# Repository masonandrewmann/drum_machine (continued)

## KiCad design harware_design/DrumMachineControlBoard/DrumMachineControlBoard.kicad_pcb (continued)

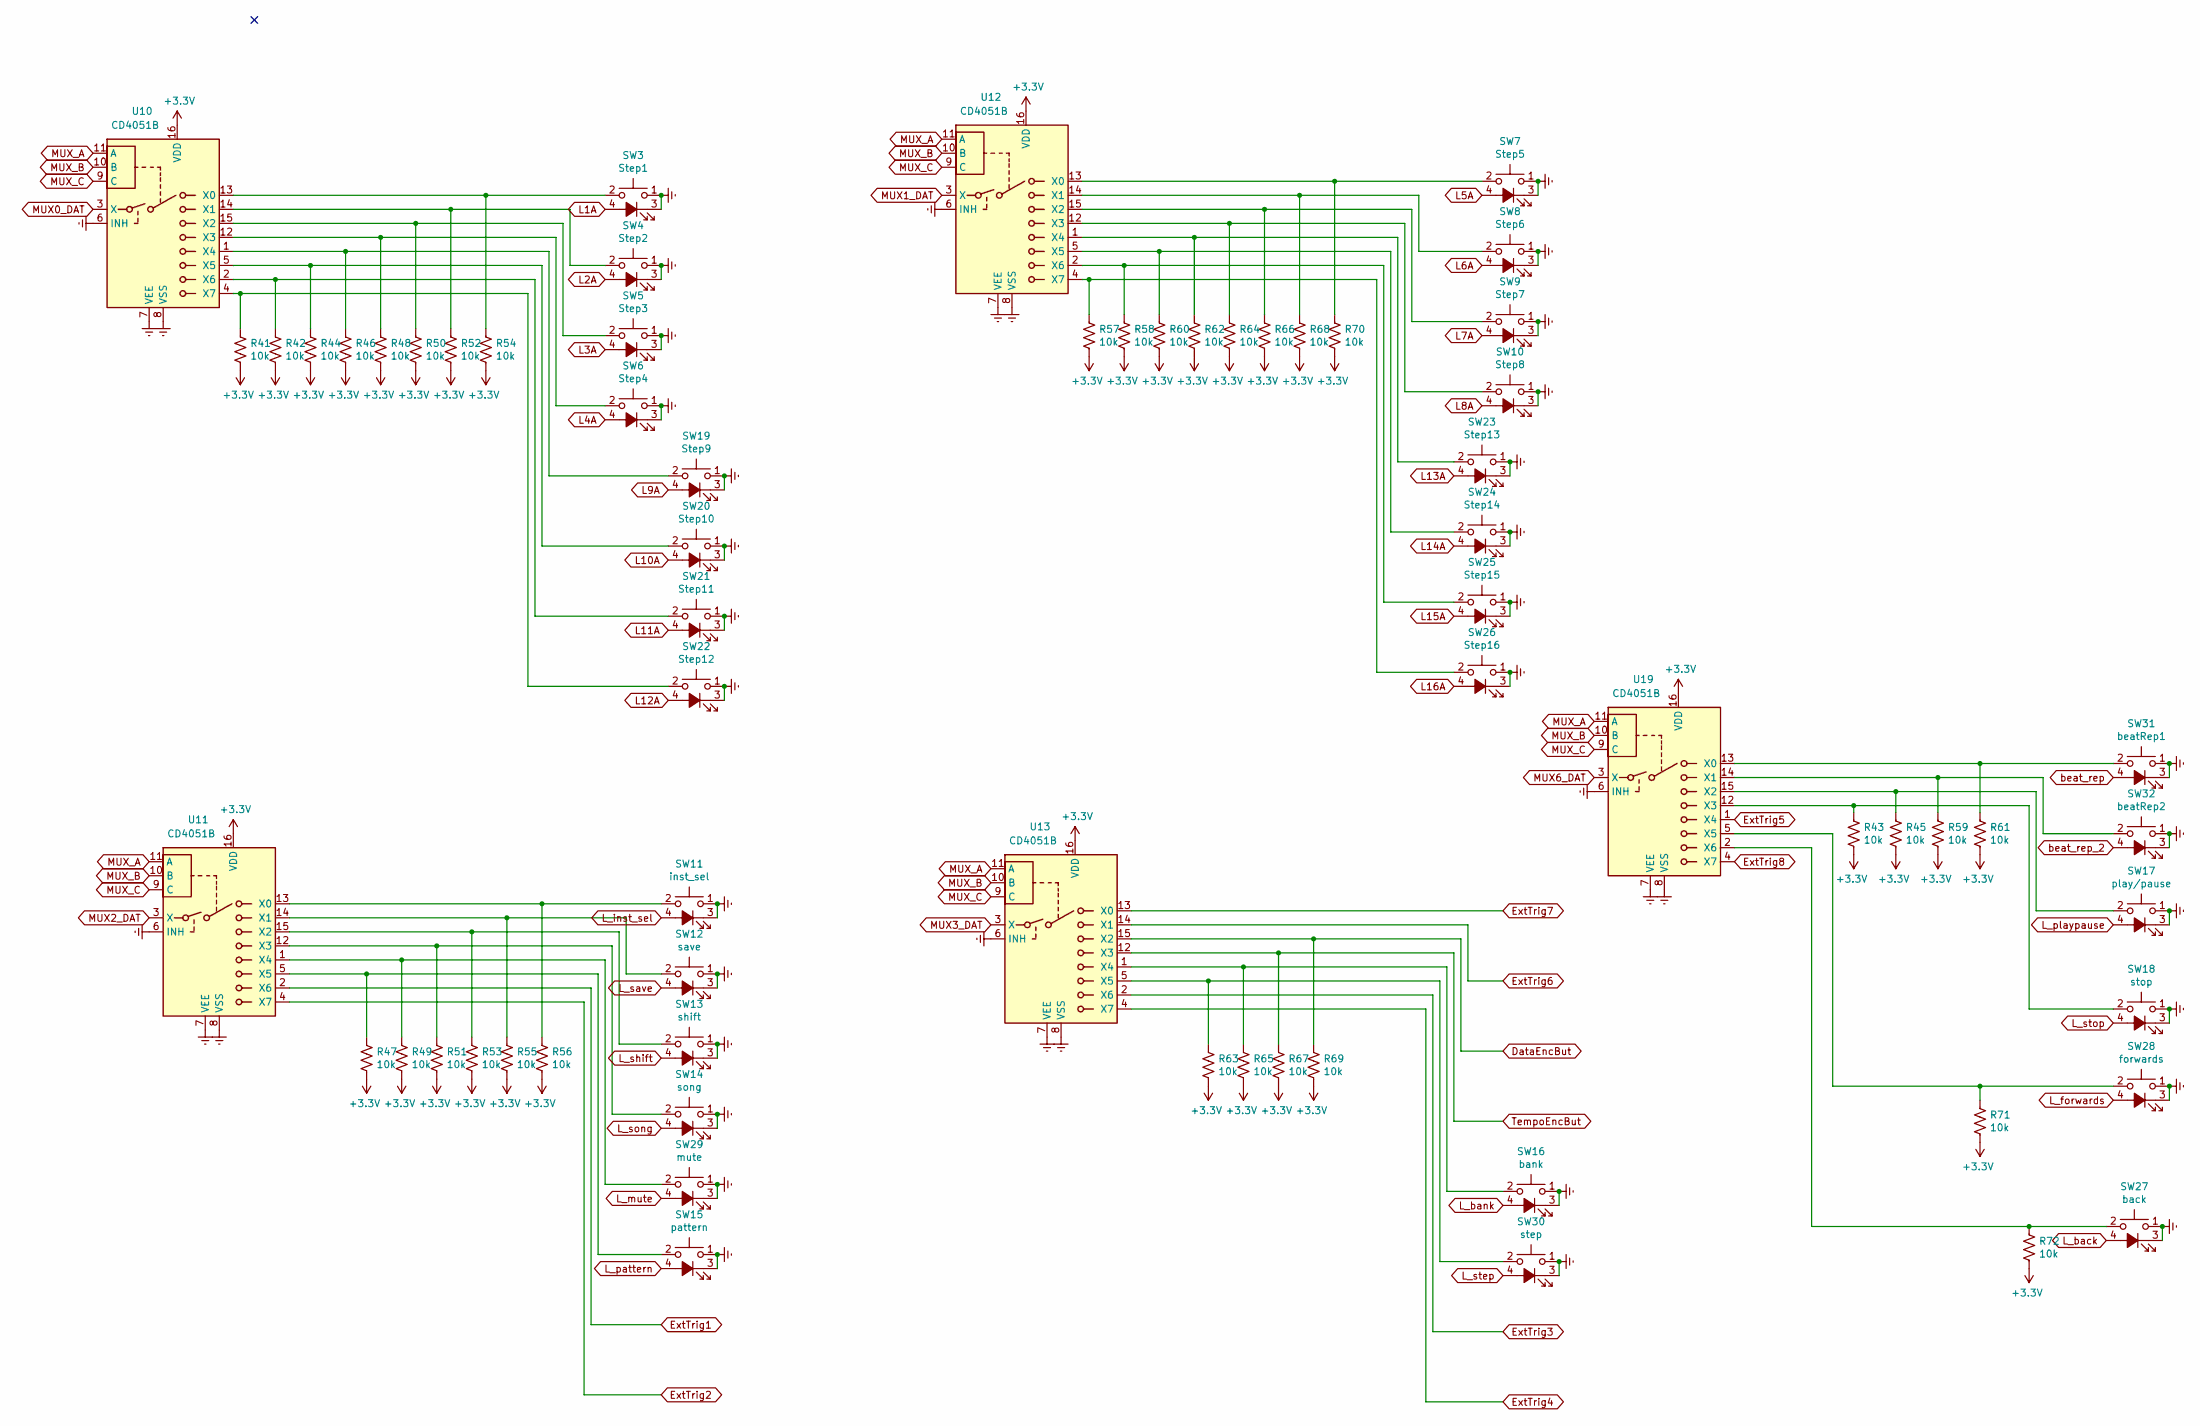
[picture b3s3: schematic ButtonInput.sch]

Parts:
R41, R42, R43, R44, R45, R46, R47, R48, R49, R50, R51, R52, R53, R54, R55, R56, R57, R58, R59, R60, R61, R62, R63, R64, R65, R66, R67, R68, R69, R70, R71, R72: 10k; R_0805_2012Metric_Pad1.15x1.40mm_HandSolder
SW3: Step1; CFPB-1CC-5G9
SW4: Step2; CFPB-1CC-5G9
SW5: Step3; CFPB-1CC-5G9
SW6: Step4; CFPB-1CC-5G9
SW7: Step5; CFPB-1CC-5G9
SW8: Step6; CFPB-1CC-5G9
SW9: Step7; CFPB-1CC-5G9
SW10: Step8; CFPB-1CC-5G9
SW11: inst_sel; CFPB-1CC-5G9
SW12: save; CFPB-1CC-5G9
SW13: shift; CFPB-1CC-5G9
SW14: song; CFPB-1CC-5G9
SW15: pattern; CFPB-1CC-5G9
SW16: bank; CFPB-1CC-5G9
SW17: play/pause; CFPB-1CC-5G9
SW18: stop; CFPB-1CC-5G9
SW19: Step9; CFPB-1CC-5G9
SW20: Step10; CFPB-1CC-5G9
SW21: Step11; CFPB-1CC-5G9
SW22: Step12; CFPB-1CC-5G9
SW23: Step13; CFPB-1CC-5G9
SW24: Step14; CFPB-1CC-5G9
SW25: Step15; CFPB-1CC-5G9
SW26: Step16; CFPB-1CC-5G9
SW27: back; CFPB-1CC-5G9
SW28: forwards; CFPB-1CC-5G9
SW29: mute; CFPB-1CC-5G9
SW30: step; CFPB-1CC-5G9
SW31: beatRep1; CFPB-1CC-5G9
SW32: beatRep2; CFPB-1CC-5G9
U10, U11, U12, U13, U19: CD4051B; SOIC-16_3.9x9.9mm_P1.27mm

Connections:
+3V3: R41.1, R42.1, R43.1, R44.1, R45.1, R46.1, R47.1, R48.1, R49.1, R50.1, R51.1, R52.1, R53.1, R54.1, R55.1, R56.1, R57.1, R58.1, R59.1, R60.1, R61.1, R62.1, R63.1, R64.1, R65.1, R66.1, R67.1, R68.1, R69.1, R70.1, R71.1, R72.1, U10.16 (VDD), U11.16 (VDD), U12.16 (VDD), U13.16 (VDD), U19.16 (VDD); also elsewhere on the board
DataEncBut: R69.2, U13.15 (X2); also elsewhere on the board
ExtTrig1: U11.2 (X6); also elsewhere on the board
ExtTrig2: U11.4 (X7); also elsewhere on the board
ExtTrig3: U13.2 (X6); also elsewhere on the board
ExtTrig4: U13.4 (X7); also elsewhere on the board
ExtTrig5: U19.1 (X4); also elsewhere on the board
ExtTrig6: U13.14 (X1); also elsewhere on the board
ExtTrig7: U13.13 (X0); also elsewhere on the board
ExtTrig8: U19.4 (X7); also elsewhere on the board
L1A: SW3.4 (A); also elsewhere on the board
L2A: SW4.4 (A); also elsewhere on the board
L3A: SW5.4 (A); also elsewhere on the board
L4A: SW6.4 (A); also elsewhere on the board
L5A: SW7.4 (A); also elsewhere on the board
L6A: SW8.4 (A); also elsewhere on the board
L7A: SW9.4 (A); also elsewhere on the board
L8A: SW10.4 (A); also elsewhere on the board
L9A: SW19.4 (A); also elsewhere on the board
L10A: SW20.4 (A); also elsewhere on the board
L11A: SW21.4 (A); also elsewhere on the board
L12A: SW22.4 (A); also elsewhere on the board
L13A: SW23.4 (A); also elsewhere on the board
L14A: SW24.4 (A); also elsewhere on the board
L15A: SW25.4 (A); also elsewhere on the board
L16A: SW26.4 (A); also elsewhere on the board
L_back: SW27.4 (A); also elsewhere on the board
L_bank: SW16.4 (A); also elsewhere on the board
L_forwards: SW28.4 (A); also elsewhere on the board
L_inst_sel: SW11.4 (A); also elsewhere on the board
L_mute: SW29.4 (A); also elsewhere on the board
L_pattern: SW15.4 (A); also elsewhere on the board
L_playpause: SW17.4 (A); also elsewhere on the board
L_save: SW12.4 (A); also elsewhere on the board
L_shift: SW13.4 (A); also elsewhere on the board
L_song: SW14.4 (A); also elsewhere on the board
L_step: SW30.4 (A); also elsewhere on the board
L_stop: SW18.4 (A); also elsewhere on the board
MUX0_DAT: U10.3 (X); also elsewhere on the board
MUX1_DAT: U12.3 (X); also elsewhere on the board
MUX2_DAT: U11.3 (X); also elsewhere on the board
MUX3_DAT: U13.3 (X); also elsewhere on the board
MUX6_DAT: U19.3 (X); also elsewhere on the board
MUX_A: U10.11 (A), U11.11 (A), U12.11 (A), U13.11 (A), U19.11 (A); also elsewhere on the board
MUX_B: U10.10 (B), U11.10 (B), U12.10 (B), U13.10 (B), U19.10 (B); also elsewhere on the board
MUX_C: U10.9 (C), U11.9 (C), U12.9 (C), U13.9 (C), U19.9 (C); also elsewhere on the board
unnamed: R41.2, SW22.2, U10.4 (X7)
unnamed: R42.2, SW21.2, U10.2 (X6)
unnamed: R43.2, SW18.2, U19.12 (X3)
unnamed: R44.2, SW20.2, U10.5 (X5)
unnamed: R45.2, SW17.2, U19.15 (X2)
unnamed: R46.2, SW19.2, U10.1 (X4)
unnamed: R47.2, SW15.2, U11.5 (X5)
unnamed: R48.2, SW6.2, U10.12 (X3)
unnamed: R49.2, SW29.2, U11.1 (X4)
unnamed: R50.2, SW5.2, U10.15 (X2)
unnamed: R51.2, SW14.2, U11.12 (X3)
unnamed: R52.2, SW4.2, U10.14 (X1)
unnamed: R53.2, SW13.2, U11.15 (X2)
unnamed: R54.2, SW3.2, U10.13 (X0)
unnamed: R55.2, SW12.2, U11.14 (X1)
unnamed: R56.2, SW11.2, U11.13 (X0)
unnamed: R57.2, SW26.2, U12.4 (X7)
unnamed: R58.2, SW25.2, U12.2 (X6)
unnamed: R59.2, SW32.2, U19.14 (X1)
unnamed: R60.2, SW24.2, U12.5 (X5)
unnamed: R61.2, SW31.2, U19.13 (X0)
unnamed: R62.2, SW23.2, U12.1 (X4)
unnamed: R63.2, SW30.2, U13.5 (X5)
unnamed: R64.2, SW10.2, U12.12 (X3)
unnamed: R65.2, SW16.2, U13.1 (X4)
unnamed: R66.2, SW9.2, U12.15 (X2)
unnamed: R68.2, SW8.2, U12.14 (X1)
unnamed: R70.2, SW7.2, U12.13 (X0)
unnamed: R71.2, SW28.2, U19.5 (X5)
unnamed: R72.2, SW27.2, U19.2 (X6)
TempoEncBut: R67.2, U13.12 (X3); also elsewhere on the board
beat_rep: SW31.4 (A); also elsewhere on the board
beat_rep_2: SW32.4 (A); also elsewhere on the board

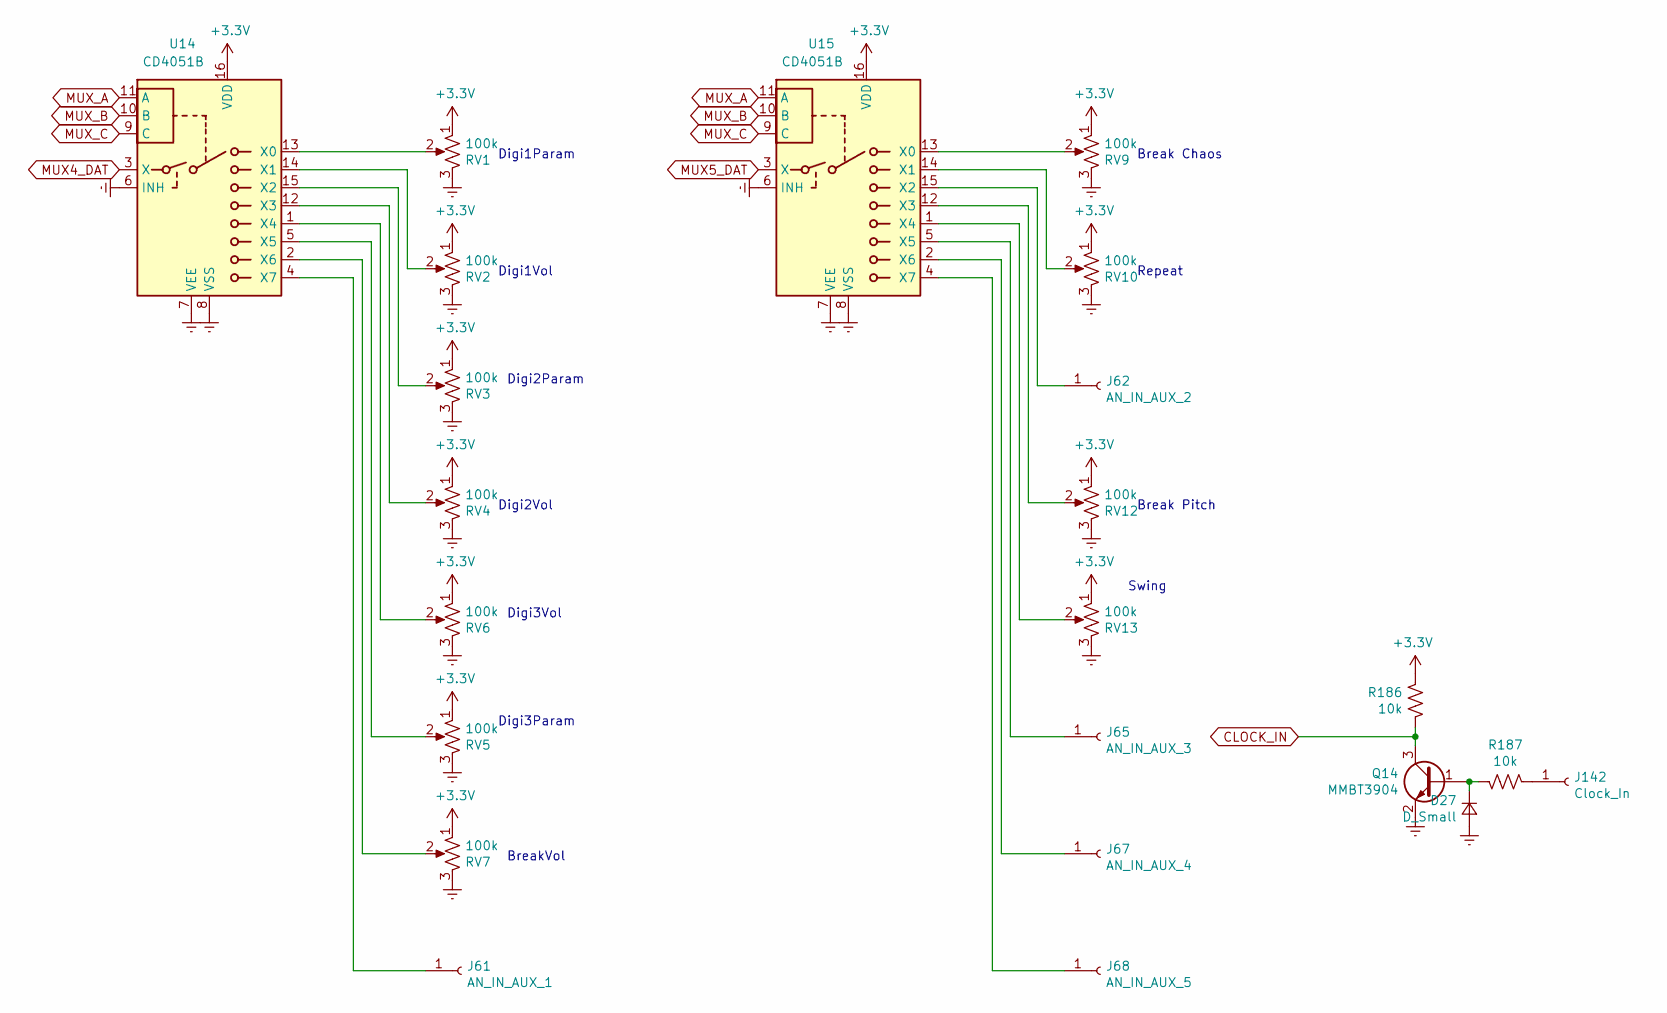
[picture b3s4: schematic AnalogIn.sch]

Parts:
D27: D_Small; D_SOD-123
J61: AN_IN_AUX_1; SolderWirePad_1x01_Drill1mm
J62: AN_IN_AUX_2; SolderWirePad_1x01_Drill1mm
J65: AN_IN_AUX_3; SolderWirePad_1x01_Drill1mm
J67: AN_IN_AUX_4; SolderWirePad_1x01_Drill1mm
J68: AN_IN_AUX_5; SolderWirePad_1x01_Drill1mm
J142: Clock_In; SolderWirePad_1x01_Drill1mm
Q14: MMBT3904; SOT-23
R186, R187: 10k; R_0603_1608Metric_Pad1.05x0.95mm_HandSolder
RV1, RV2, RV3, RV4, RV5, RV6, RV7, RV9, RV10, RV12, RV13: 100k; masonsPotentiometer_Alpha_RD901F-40-00D_Single_Vertical
U14, U15: CD4051B; SOIC-16_3.9x9.9mm_P1.27mm

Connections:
+3V3: R186.2, RV1.1, RV2.1, RV3.1, RV4.1, RV5.1, RV6.1, RV7.1, RV9.1, RV10.1, RV12.1, RV13.1, U14.16 (VDD), U15.16 (VDD); also elsewhere on the board
CLOCK_IN: Q14.3 (C), R186.1; also elsewhere on the board
MUX4_DAT: U14.3 (X); also elsewhere on the board
MUX5_DAT: U15.3 (X); also elsewhere on the board
MUX_A: U14.11 (A), U15.11 (A); also elsewhere on the board
MUX_B: U14.10 (B), U15.10 (B); also elsewhere on the board
MUX_C: U14.9 (C), U15.9 (C); also elsewhere on the board
unnamed: D27.1 (K), Q14.1 (B), R187.1
unnamed: J61.1, U14.4 (X7)
unnamed: J62.1, U15.15 (X2)
unnamed: J65.1, U15.5 (X5)
unnamed: J67.1, U15.2 (X6)
unnamed: J68.1, U15.4 (X7)
unnamed: J142.1, R187.2
unnamed: RV1.2, U14.13 (X0)
unnamed: RV2.2, U14.14 (X1)
unnamed: RV3.2, U14.15 (X2)
unnamed: RV4.2, U14.12 (X3)
unnamed: RV5.2, U14.5 (X5)
unnamed: RV6.2, U14.1 (X4)
unnamed: RV7.2, U14.2 (X6)
unnamed: RV9.2, U15.13 (X0)
unnamed: RV10.2, U15.14 (X1)
unnamed: RV12.2, U15.12 (X3)
unnamed: RV13.2, U15.1 (X4)

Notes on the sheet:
Digi1Param
Digi2Param
Digi3Param
Digi1Vol
Digi2Vol
Digi3Vol
BreakVol
Break Chaos
Repeat
Break Pitch
Swing

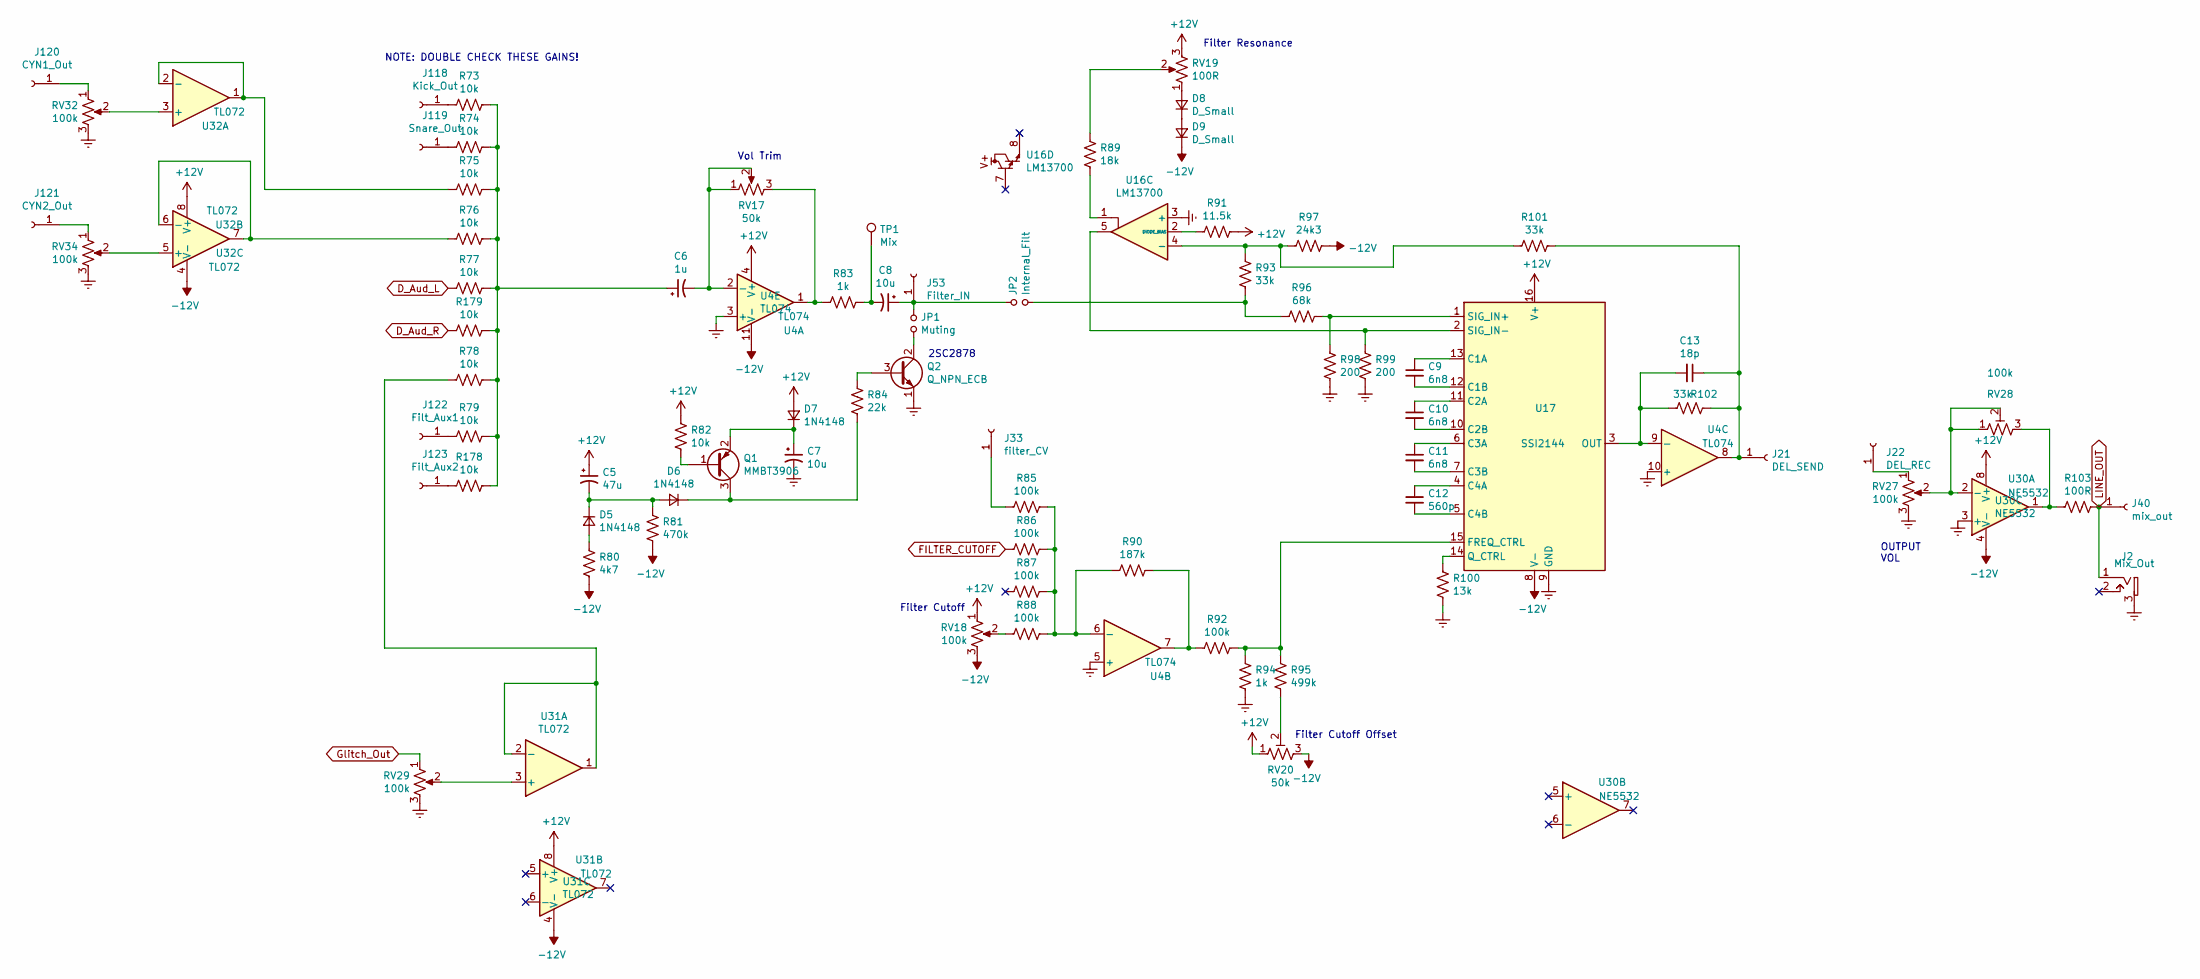
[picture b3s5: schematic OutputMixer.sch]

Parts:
C5: 47u; CP_Elec_6.3x7.7
C6: 1u; CP_Elec_4x4.5
C7, C8: 10u; CP_Elec_4x4.5
C9, C10, C11: 6n8; C_0805_2012Metric_Pad1.15x1.40mm_HandSolder
C12: 560p; C_0805_2012Metric_Pad1.15x1.40mm_HandSolder
C13: 18p; C_0805_2012Metric_Pad1.15x1.40mm_HandSolder
D5, D6, D7: 1N4148; D_SOD-123
D8, D9: D_Small; D_SOD-123
J2: Mix_Out; SolderWirePad_1x01_Drill1mm
J21: DEL_SEND; SolderWirePad_1x01_Drill1mm
J22: DEL_REC; SolderWirePad_1x01_Drill1mm
J33: filter_CV; SolderWirePad_1x01_Drill1mm
J40: mix_out; SolderWirePad_1x01_Drill1mm
J53: Filter_IN; SolderWirePad_1x01_Drill1mm
J118: Kick_Out; SolderWirePad_1x01_Drill1mm
J119: Snare_Out; SolderWirePad_1x01_Drill1mm
J120: CYN1_Out; SolderWirePad_1x01_Drill1mm
J121: CYN2_Out; SolderWirePad_1x01_Drill1mm
J122: Filt_Aux1; SolderWirePad_1x01_Drill1mm
J123: Filt_Aux2; SolderWirePad_1x01_Drill1mm
JP1: Muting; SolderJumper-2_P1.3mm_Open_RoundedPad1.0x1.5mm
JP2: Internal_Filt; SolderJumper-2_P1.3mm_Open_RoundedPad1.0x1.5mm
Q1: MMBT3906; SOT-23
Q2: Q_NPN_ECB; TO-92_Inline_Wide
R73, R74, R75, R76, R77, R78, R79, R82, R178, R179: 10k; R_0805_2012Metric_Pad1.15x1.40mm_HandSolder
R80: 4k7; R_0805_2012Metric_Pad1.15x1.40mm_HandSolder
R81: 470k; R_0805_2012Metric_Pad1.15x1.40mm_HandSolder
R83, R94: 1k; R_0805_2012Metric_Pad1.15x1.40mm_HandSolder
R84: 22k; R_0805_2012Metric_Pad1.15x1.40mm_HandSolder
R85, R86, R87, R88, R92: 100k; R_0805_2012Metric_Pad1.15x1.40mm_HandSolder
R89: 18k; R_0805_2012Metric_Pad1.15x1.40mm_HandSolder
R90: 187k; R_0805_2012Metric_Pad1.15x1.40mm_HandSolder
R91: 11.5k; R_0805_2012Metric_Pad1.15x1.40mm_HandSolder
R93, R101, R102: 33k; R_0805_2012Metric_Pad1.15x1.40mm_HandSolder
R95: 499k; R_0805_2012Metric_Pad1.15x1.40mm_HandSolder
R96: 68k; R_0805_2012Metric_Pad1.15x1.40mm_HandSolder
R97: 24k3; R_0805_2012Metric_Pad1.15x1.40mm_HandSolder
R98, R99: 200; R_0805_2012Metric_Pad1.15x1.40mm_HandSolder
R100: 13k; R_0805_2012Metric_Pad1.15x1.40mm_HandSolder
R103: 100R; R_0805_2012Metric_Pad1.15x1.40mm_HandSolder
RV17, RV20: 50k; Potentiometer_Runtron_RM-065_Vertical
RV18, RV27, RV29, RV32, RV34: 100k; masonsPotentiometer_Alpha_RD901F-40-00D_Single_Vertical
RV19: 100R; masonsPotentiometer_Alpha_RD901F-40-00D_Single_Vertical
RV28: 100k; Potentiometer_Runtron_RM-065_Vertical
TP1: Mix; TestPoint_Loop_D2.50mm_Drill1.0mm
U4: TL074; SOIC-14_3.9x8.7mm_P1.27mm
U16: LM13700; SOIC-16_3.9x9.9mm_P1.27mm
U17: SSI2144; SSOP-16_3.9x4.9mm_P0.635mm
U30: NE5532; DIP-8_W7.62mm_Socket
U31, U32: TL072; SOIC-8_3.9x4.9mm_P1.27mm

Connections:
-12V: D9.1 (K), R80.1, R81.1, R97.1, RV18.3, RV20.3, U4.11 (V-), U17.8 (V-), U30.4 (V-), U31.4 (V-), U32.4 (V-); also elsewhere on the board
D_Aud_L: R77.2; also elsewhere on the board
D_Aud_R: R179.2; also elsewhere on the board
FILTER_CUTOFF: R86.2; also elsewhere on the board
Glitch_Out: RV29.1; also elsewhere on the board
unnamed: C5.2, D5.1 (K), D6.2 (A), R81.2
unnamed: C6.1, R73.1, R74.1, R75.1, R76.1, R77.1, R78.1, R79.1, R178.1, R179.1
unnamed: C6.2, RV17.1, RV17.2, U4.2 (-)
unnamed: C7.1, D7.1 (K), Q1.2 (E)
unnamed: C8.1, J53.1, JP1.1, JP2.1
unnamed: C8.2, R83.1, TP1.1
unnamed: C9.1, U17.13 (C1A)
unnamed: C9.2, U17.12 (C1B)
unnamed: C10.1, U17.11 (C2A)
unnamed: C10.2, U17.10 (C2B)
unnamed: C11.1, U17.6 (C3A)
unnamed: C11.2, U17.7 (C3B)
unnamed: C12.1, U17.4 (C4A)
unnamed: C12.2, U17.5 (C4B)
unnamed: C13.1, J21.1, R101.1, R102.2, U4.8
unnamed: C13.2, R102.1, U4.9 (-), U17.3 (OUT)
unnamed: D5.2 (A), R80.2
unnamed: D6.1 (K), Q1.3 (C), R84.1
unnamed: D8.1 (K), D9.2 (A)
unnamed: D8.2 (A), RV19.1
unnamed: J22.1, RV27.1
unnamed: J33.1, R85.2
unnamed: J118.1, R73.2
unnamed: J119.1, R74.2
unnamed: J120.1, RV32.1
unnamed: J121.1, RV34.1
unnamed: J122.1, R79.2
unnamed: J123.1, R178.2
unnamed: JP1.2, Q2.2 (C)
unnamed: JP2.2, R93.2, R96.1
unnamed: Q1.1 (B), R82.1
unnamed: Q2.3 (B), R84.2
unnamed: R75.2, U32.1, U32.2 (-)
unnamed: R76.2, U32.6 (-), U32.7
unnamed: R78.2, U31.1, U31.2 (-)
unnamed: R83.2, RV17.3, U4.1
unnamed: R85.1, R86.1, R87.1, R88.1, R90.2, U4.6 (-)
unnamed: R88.2, RV18.2
unnamed: R89.1, RV19.2
unnamed: R89.2, U16.1
unnamed: R90.1, R92.2, U4.7
unnamed: R91.2, U16.2 (DIODE_BIAS)
unnamed: R92.1, R94.2, R95.2, U17.15 (FREQ_CTRL)
unnamed: R95.1, RV20.2
unnamed: R96.2, R98.2, U17.1 (SIG_IN+)
unnamed: R99.2, U16.5, U17.2 (SIG_IN-)
unnamed: R100.2, U17.14 (Q_CTRL)
unnamed: R93.1, R97.2, R101.2, U16.4 (-)
unnamed: R103.2, RV28.3, U30.1
unnamed: RV27.2, RV28.1, RV28.2, U30.2 (-)
unnamed: RV29.2, U31.3 (+)
unnamed: RV32.2, U32.3 (+)
unnamed: RV34.2, U32.5 (+)

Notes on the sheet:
NOTE: DOUBLE CHECK THESE GAINS!
Filter Cutoff Offset
Filter Resonance
Filter Cutoff
Vol Trim
2SC2878
OUTPUT VOL

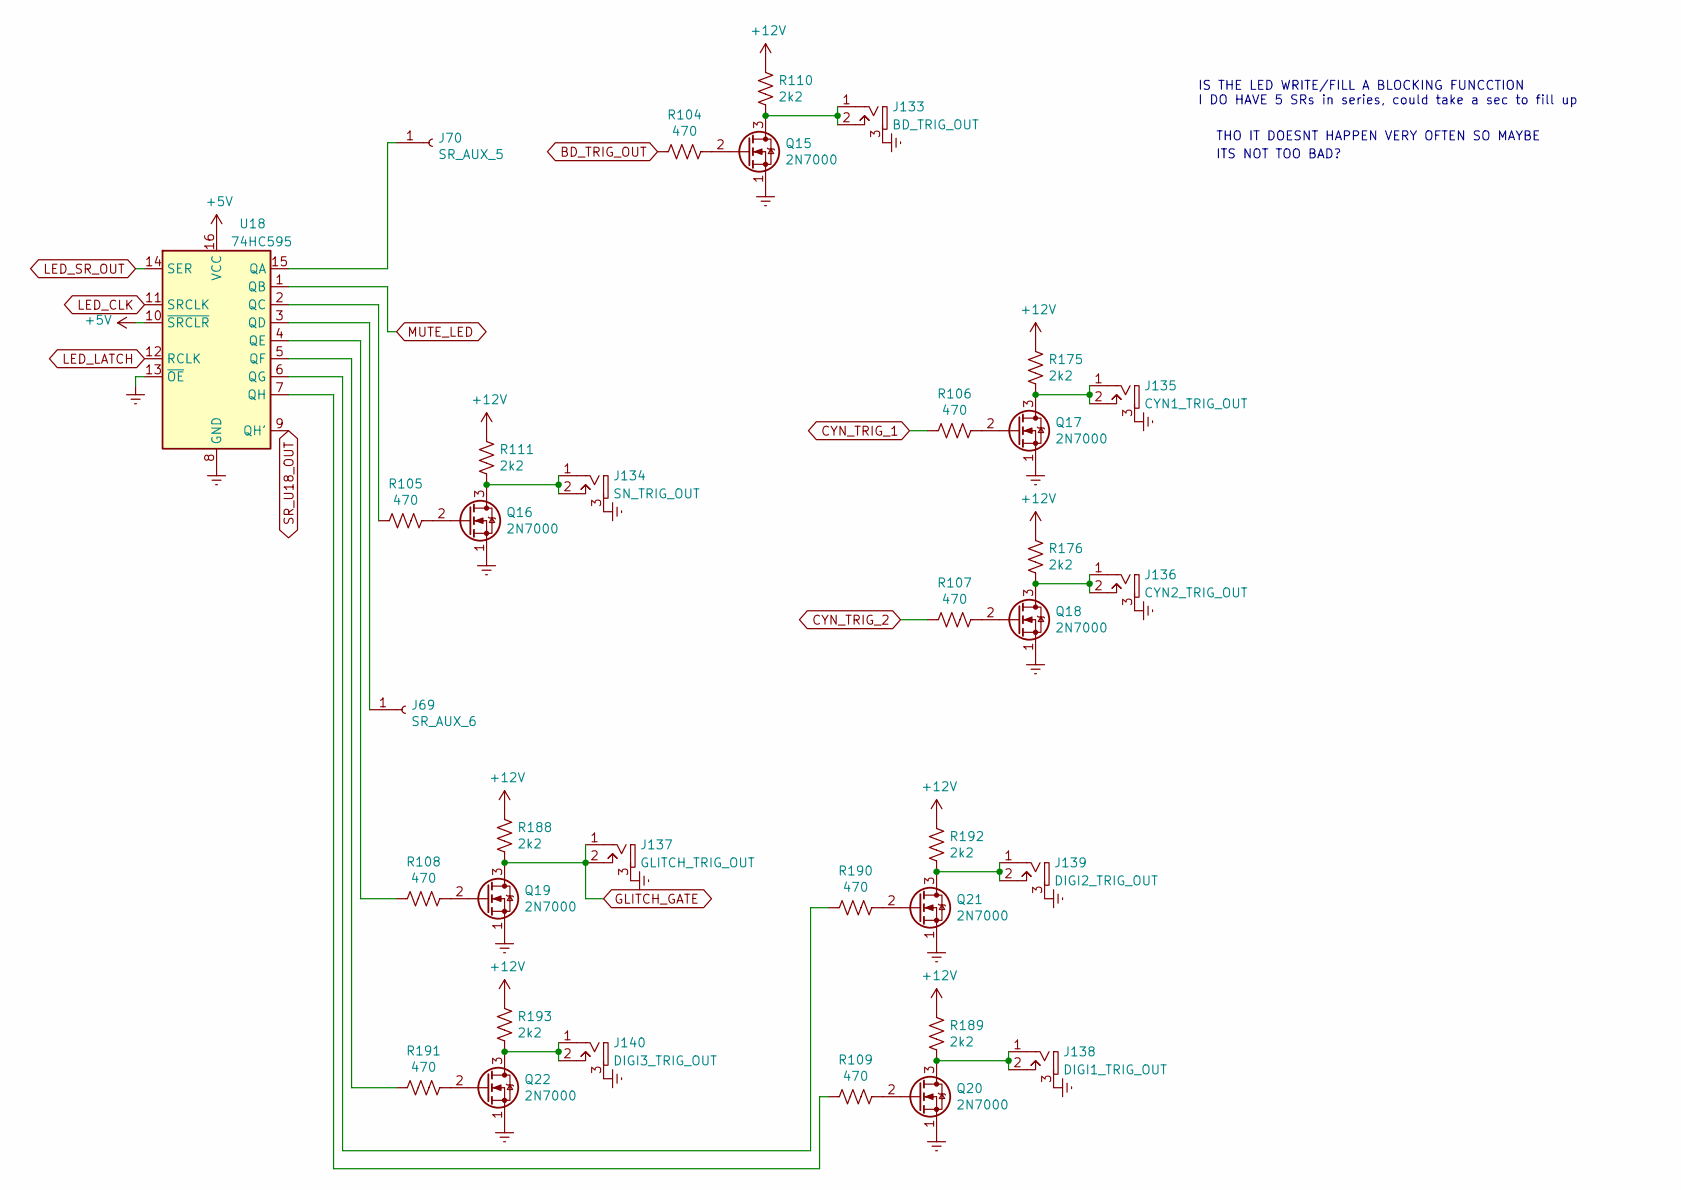
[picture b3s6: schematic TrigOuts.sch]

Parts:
J69: SR_AUX_6; SolderWirePad_1x01_Drill1mm
J70: SR_AUX_5; SolderWirePad_1x01_Drill1mm
J133: BD_TRIG_OUT; PJ301-BM
J134: SN_TRIG_OUT; PJ301-BM
J135: CYN1_TRIG_OUT; PJ301-BM
J136: CYN2_TRIG_OUT; PJ301-BM
J137: GLITCH_TRIG_OUT; PJ301-BM
J138: DIGI1_TRIG_OUT; PJ301-BM
J139: DIGI2_TRIG_OUT; PJ301-BM
J140: DIGI3_TRIG_OUT; PJ301-BM
Q15, Q16, Q17, Q18, Q19, Q20, Q21, Q22: 2N7000; SOT-23_Handsoldering
R104, R105, R106, R107, R108, R109, R190, R191: 470; R_0603_1608Metric_Pad1.05x0.95mm_HandSolder
R110, R111, R175, R176, R188, R189, R192, R193: 2k2; R_0603_1608Metric_Pad1.05x0.95mm_HandSolder
U18: 74HC595; SOIC-16_3.9x9.9mm_P1.27mm

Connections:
+5V: U18.10 (~SRCLR), U18.16 (VCC); also elsewhere on the board
BD_TRIG_OUT: R104.2; also elsewhere on the board
CYN_TRIG_1: R106.2; also elsewhere on the board
CYN_TRIG_2: R107.2; also elsewhere on the board
GLITCH_GATE: J137.1, J137.2, Q19.3 (D), R188.2; also elsewhere on the board
LED_CLK: U18.11 (SRCLK); also elsewhere on the board
LED_LATCH: U18.12 (RCLK); also elsewhere on the board
LED_SR_OUT: U18.14 (SER); also elsewhere on the board
MUTE_LED: U18.1 (QB); also elsewhere on the board
unnamed: J69.1, U18.3 (QD)
unnamed: J70.1, U18.15 (QA)
unnamed: J133.1, J133.2, Q15.3 (D), R110.2
unnamed: J134.1, J134.2, Q16.3 (D), R111.2
unnamed: J135.1, J135.2, Q17.3 (D), R175.2
unnamed: J136.1, J136.2, Q18.3 (D), R176.2
unnamed: J138.1, J138.2, Q20.3 (D), R189.2
unnamed: J139.1, J139.2, Q21.3 (D), R192.2
unnamed: J140.1, J140.2, Q22.3 (D), R193.2
unnamed: Q15.2 (G), R104.1
unnamed: Q16.2 (G), R105.1
unnamed: Q17.2 (G), R106.1
unnamed: Q18.2 (G), R107.1
unnamed: Q19.2 (G), R108.1
unnamed: Q20.2 (G), R109.1
unnamed: Q21.2 (G), R190.1
unnamed: Q22.2 (G), R191.1
unnamed: R105.2, U18.2 (QC)
unnamed: R108.2, U18.4 (QE)
unnamed: R109.2, U18.7 (QH)
unnamed: R190.2, U18.6 (QG)
unnamed: R191.2, U18.5 (QF)
SR_U18_OUT: U18.9 (QH'); also elsewhere on the board

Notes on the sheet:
IS THE LED WRITE/FILL A BLOCKING FUNCCTION I DO HAVE 5 SRs in series, could take a sec to fill up
THO IT DOESNT HAPPEN VERY OFTEN SO MAYBE
ITS NOT TOO BAD?

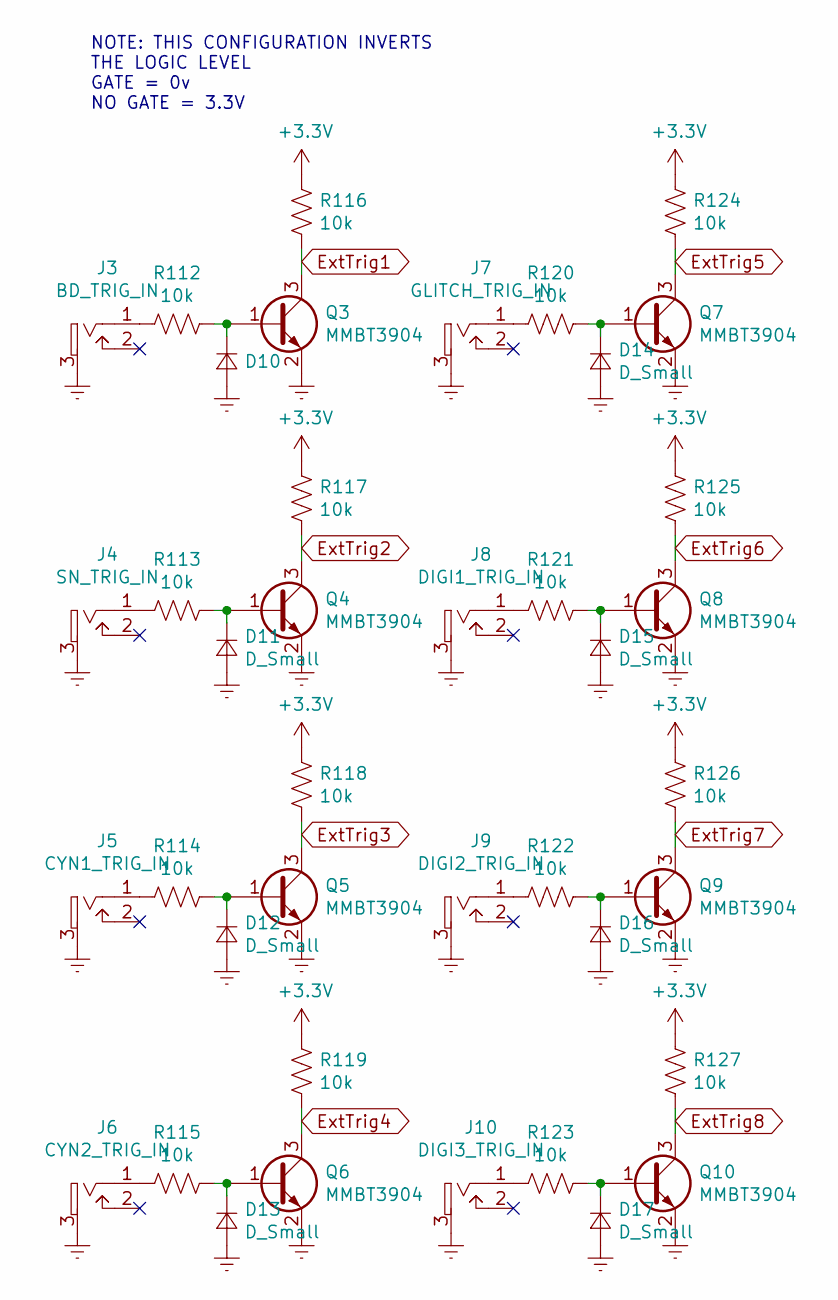
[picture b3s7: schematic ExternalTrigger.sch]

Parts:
D10, D11, D12, D13, D14, D15, D16, D17: D_Small; D_SOD-123
J3: BD_TRIG_IN; PJ301-BM
J4: SN_TRIG_IN; PJ301-BM
J5: CYN1_TRIG_IN; PJ301-BM
J6: CYN2_TRIG_IN; PJ301-BM
J7: GLITCH_TRIG_IN; PJ301-BM
J8: DIGI1_TRIG_IN; PJ301-BM
J9: DIGI2_TRIG_IN; PJ301-BM
J10: DIGI3_TRIG_IN; PJ301-BM
Q3, Q4, Q5, Q6, Q7, Q8, Q9, Q10: MMBT3904; SOT-23
R112, R113, R114, R115, R116, R117, R118, R119, R120, R121, R122, R123, R124, R125, R126, R127: 10k; R_0603_1608Metric_Pad1.05x0.95mm_HandSolder

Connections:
+3V3: R116.2, R117.2, R118.2, R119.2, R124.2, R125.2, R126.2, R127.2; also elsewhere on the board
ExtTrig1: Q3.3 (C), R116.1; also elsewhere on the board
ExtTrig2: Q4.3 (C), R117.1; also elsewhere on the board
ExtTrig3: Q5.3 (C), R118.1; also elsewhere on the board
ExtTrig4: Q6.3 (C), R119.1; also elsewhere on the board
ExtTrig5: Q7.3 (C), R124.1; also elsewhere on the board
ExtTrig6: Q8.3 (C), R125.1; also elsewhere on the board
ExtTrig7: Q9.3 (C), R126.1; also elsewhere on the board
ExtTrig8: Q10.3 (C), R127.1; also elsewhere on the board
unnamed: D10.1 (K), Q3.1 (B), R112.1
unnamed: D11.1 (K), Q4.1 (B), R113.1
unnamed: D12.1 (K), Q5.1 (B), R114.1
unnamed: D13.1 (K), Q6.1 (B), R115.1
unnamed: D14.1 (K), Q7.1 (B), R120.1
unnamed: D15.1 (K), Q8.1 (B), R121.1
unnamed: D16.1 (K), Q9.1 (B), R122.1
unnamed: D17.1 (K), Q10.1 (B), R123.1
unnamed: J3.1, R112.2
unnamed: J4.1, R113.2
unnamed: J5.1, R114.2
unnamed: J6.1, R115.2
unnamed: J7.1, R120.2
unnamed: J8.1, R121.2
unnamed: J9.1, R122.2
unnamed: J10.1, R123.2

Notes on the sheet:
NOTE: THIS CONFIGURATION INVERTS THE LOGIC LEVEL GATE = 0v NO GATE = 3.3V
